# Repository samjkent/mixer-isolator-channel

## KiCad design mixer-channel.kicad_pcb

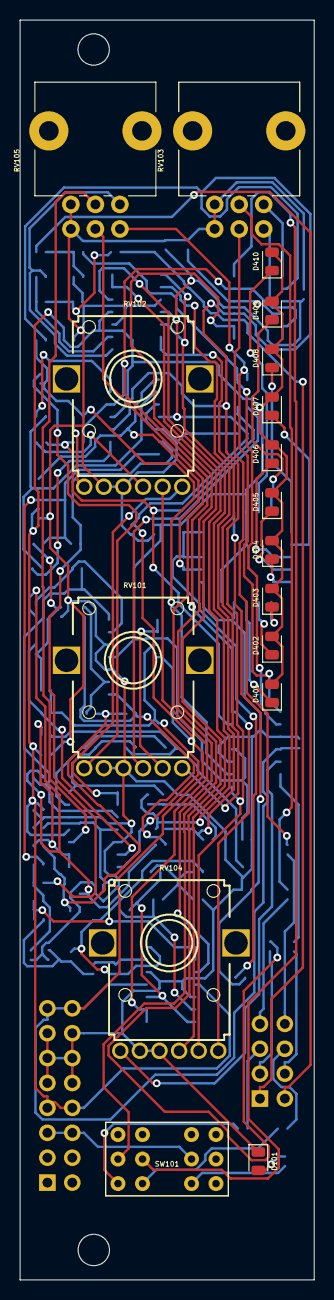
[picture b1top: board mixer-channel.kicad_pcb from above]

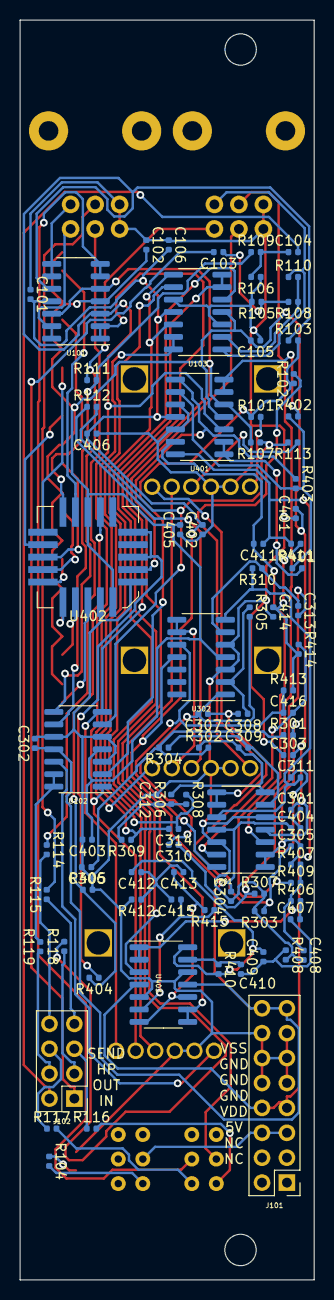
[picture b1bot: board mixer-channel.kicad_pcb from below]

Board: 2 copper layers, 30.0 x 128.5 mm, 107 parts (90 on the bottom side), 88 nets.

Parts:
C101, C102, C105, C106, C301, C302, C303, C304, C401, C402, C403, C404, C405, C406: 0.1uF; C_0402_1005Metric
C103, C104: 2.2uF; C_0402_1005Metric
C305, C307, C308, C310, C311, C313, C407, C409, C410, C412, C413, C415: 2.7nF; C_0402_1005Metric
C306, C312, C408, C414: 39nF; C_0402_1005Metric
C309, C314, C411, C416: 4.7nF; C_0402_1005Metric
D101, D401, D402, D403, D404, D405, D406, D407, D408, D409, D410: LED; LED_0805_2012Metric
J101: Conn_02x08_Odd_Even; PinHeader_2x08_P2.54mm_Vertical
J102: Conn_02x04_Counter_Clockwise; PinHeader_2x04_P2.54mm_Vertical
R101, R102, R103, R107, R108, R109, R112, R113, R114, R115, R116, R117, R118, R119, R401, R402, R403: 10k; R_0402_1005Metric
R104: 220; R_0402_1005Metric
R105, R106: 7.5k; R_0402_1005Metric
R110, R111: 50k; R_0402_1005Metric
R301, R302, R306, R308, R406, R407, R411, R413: 54.9K; R_0402_1005Metric
R303, R307, R408, R412: 32.4k; R_0402_1005Metric
R304, R309, R409, R414: 27.4K; R_0402_1005Metric
R305, R310, R410, R415: 294k; R_0402_1005Metric
R404: 1.2k; R_0402_1005Metric
R405: 3.8k; R_0402_1005Metric
RV101: LP; PTV112
RV102: HP; PTV112
RV103: SEND; Potentiometer_Alps_RK09L_Double_Vertical
RV104: FADER; PTV112
RV105: INPUT_GAIN; Potentiometer_Alps_RK09L_Double_Vertical
SW101: SW_4PDT_x4; MHPS4284
U101, U102, U103, U301, U302, U401, U403: TL074; SOIC-14_3.9x8.7mm_P1.27mm
U402: LM3916; PLCC-20-LongPads

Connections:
+5V: J101.5, J101.6, SW101.8
/HP_OUT_L: J102.5, R116.1
/HP_OUT_R: J102.6, R117.1
/INPUT_L: C103.2, J102.1
/INPUT_R: C104.2, J102.2
/L: RV105.2, U301.3
/L_PF: RV104.5, U103.5
/OUTPUT_L: J102.3, R118.1
/OUTPUT_R: J102.4, R119.1
/R: RV105.5, U403.3
/R_PF: RV104.2, U102.12
/SEND_OUT_L: J102.7, R115.1
/SEND_OUT_R: J102.8, R114.2
/Sheet6029FE99/HP: RV102.3, U301.8, U301.9
/Sheet6029FE99/LP: RV101.3, U103.13, U103.14
/VU_L: R103.1, RV104.6, U101.3, U101.10, U102.1, U401.3
/VU_R: R107.2, RV104.3, U101.5, U101.12, U102.7, U401.5
/sheet602F44A0/HP: RV102.6, U403.8, U403.9
/sheet602F44A0/LP: RV101.6, U302.8, U302.9
GND: C101.1, C102.1, C105.1, C106.1, C301.2, C302.2, C303.1, C304.1, C306.2, C312.2, C401.1, C402.1, C403.2, C404.2, C405.1, C406.1, C408.2, C414.2, D101.1, J101.9, J101.10, J101.11, J101.12, J101.13, J101.14, R105.2, R106.1, R303.2, R307.2, R405.2, R408.2, R412.2, RV101.1, RV101.4, RV102.1, RV102.4, RV103.1, RV103.4, RV104.1, RV104.4, RV105.1, RV105.4, U102.3, U102.5, U102.10, U103.3, U103.10, U301.5, U301.12, U302.3, U302.5, U401.10, U401.12, U402.2, U402.4, U403.5, U403.12
unnamed: C103.1, R105.1, R108.2
unnamed: C104.1, R106.2, R109.2
unnamed: C305.1, C307.1, C308.2, R303.1
unnamed: C305.2, R301.2, U301.1, U301.2
unnamed: C306.1, R301.1, R302.2, R304.2
unnamed: C307.2, C310.2, R305.2, U302.1
unnamed: C308.1, R305.1, U302.2
unnamed: C309.1, R302.1, R306.2, U301.7
unnamed: C309.2, R304.1, U301.6
unnamed: C310.1, C311.1, C313.2, R307.1
unnamed: C311.2, R310.2, U301.10, U302.7
unnamed: C312.1, R306.1, R308.2, R309.2
unnamed: C313.1, R310.1, U302.6
unnamed: C314.1, R308.1, U103.8, U103.12
unnamed: C314.2, R309.1, U103.9
unnamed: C407.1, C409.1, C410.2, R408.1
unnamed: C407.2, R406.2, U403.1, U403.2
unnamed: C408.1, R406.1, R407.2, R409.2
unnamed: C409.2, C412.2, R410.2, U403.14
unnamed: C410.1, R410.1, U403.13
unnamed: C411.1, R407.1, R411.2, U401.14
unnamed: C411.2, R409.1, U401.13
unnamed: C412.1, C413.1, C415.2, R412.1
unnamed: C413.2, R415.2, U403.7, U403.10
unnamed: C414.1, R411.1, R413.2, R414.2
unnamed: C415.1, R415.1, U403.6
unnamed: C416.1, R413.1, U301.14, U302.10
unnamed: C416.2, R414.1, U301.13
unnamed: D101.2, R104.1
unnamed: D401.1, U402.1
unnamed: D402.1, U402.20
unnamed: D403.1, U402.19
unnamed: D404.1, U402.18
unnamed: D405.1, U402.17
unnamed: D406.1, U402.16
unnamed: D407.1, U402.15
unnamed: D408.1, U402.14
unnamed: D409.1, U402.13
unnamed: D410.1, U402.12
unnamed: R101.1, R102.1, R103.2, U102.2
unnamed: R101.2, RV102.2
unnamed: R102.2, RV101.2
unnamed: R104.2, SW101.9
unnamed: R107.1, R112.2, R113.2, U102.6
unnamed: R108.1, R110.2, U103.2
unnamed: R109.1, R111.2, U102.9
unnamed: R110.1, RV105.3, U103.1
unnamed: R111.1, RV105.6, U102.8
unnamed: R112.1, RV101.5
unnamed: R113.1, RV102.5
unnamed: R114.1, RV103.5
unnamed: R115.2, RV103.2
unnamed: R116.2, SW101.3
unnamed: R117.2, SW101.6
unnamed: R118.2, U103.6, U103.7
unnamed: R119.2, U102.13, U102.14
unnamed: R401.1, R402.1, R403.2, U401.9
unnamed: R401.2, U401.1, U401.2
unnamed: R402.2, U401.6, U401.7
unnamed: R403.1, U401.8, U402.5
unnamed: R404.1, U402.6, U402.8
unnamed: R404.2, R405.1, U402.10
unnamed: RV103.3, U101.8, U101.9
unnamed: RV103.6, U101.13, U101.14
unnamed: SW101.2, U101.1, U101.2
unnamed: SW101.5, U101.6, U101.7
VDD: C102.2, C105.2, C301.1, C303.2, C401.2, C403.1, C405.2, D401.2, D402.2, D403.2, D404.2, D405.2, D406.2, D407.2, D408.2, D409.2, D410.2, J101.7, J101.8, U101.4, U102.4, U103.4, U301.4, U302.4, U401.4, U402.3, U402.11, U403.4
VSS: C101.2, C106.2, C302.1, C304.2, C402.2, C404.1, C406.2, J101.15, J101.16, U101.11, U102.11, U103.11, U301.11, U302.11, U401.11, U403.11

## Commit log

2021-03-01 Add blank readme
2021-03-01 Create LICENSE
2021-07-28 Stop cue button from shorting against mounting rails
